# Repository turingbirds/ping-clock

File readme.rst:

The Ping Clock
==============

Are you ever in a video call, when the other party suddenly freezes mid-sentence, leaving you wondering after a few seconds of silence: is it my connection that's having issues, or theirs? In such situations, one glance at the ping clock dial provides an immediate overview of your internet connection status and health, measured in terms of ping time.

Ping time is the time it takes for a network packet to reach a certain destination host and come back again. Lower is better; for video calls, anything below a few tenths of a second is typically fine. The host can be chosen as a public server with high reliability (for example, google.com or 8.8.8.8), or as something with a special significance (like the hostname of your cloud instance).

If your video call freezes, but the ping clock continues to indicate low ping, there is no need to reset your router; just wait for the other side to come back.

.. table::
   :align: center

   +-------------------------------------------------------------------------------------------------------------------------------------------------------------+
   | 🢧  `Click here for a video of the ping clock in action <https://github.com/turingbirds/ping-clock/blob/master/fig/ping_clock_movie.mp4?raw=true>`_        🢠 |
   +-------------------------------------------------------------------------------------------------------------------------------------------------------------+

.. figure:: fig/ping_clock.jpeg
   :scale: 10 %
   :align: left

Setting up the wifi network and host to ping is done by connecting to the ping clock's wifi access point. After configuration, the outermost hand will update once each second with the latest ping value, while the innermost hand tracks the recent maximum pings, making an intermittent connection easy to see.

.. |screenshot1| image:: fig/screenshot1.png
    :scale: 20%

.. |screenshot2| image:: fig/screenshot2.png
    :scale: 20%

.. table::
   :align: center

   +---------------+---------------+
   | |screenshot2| | |screenshot1| |
   +---------------+---------------+

Hardware
--------

The system is controlled by an ESP32, which connects via wifi and updates the e-paper display, and then performs the ping, computes the desired clock hand angles, and sends this angle via SPI to a second ESP32, which functions exclusively as a motor controller.

.. image:: fig/diag.png
   :alt: System block diagram

For mounting the components to the frontplate, a template is provided in `frontplate-cad/frontplate_cnc.pdf <https://github.com/turingbirds/ping-clock/blob/master/frontplate-cad/frontplate_cnc.pdf>`_. Drill out all the holes marked in pink, then drill out all the M3 screw holes at half depth in a larger diameter, to create holes for the countersunk screw heads. The frontplate decal then lies flat against the front, covering all the screws. The front of the e-paper display is pressed against the back of the faceplace, held in place by two aluminium bars covered in a layer of foam.
   
.. image:: fig/ping_clock_rear.jpeg
   :alt: Rear view of the ping clock

The clock is powered from a 5 V DC supply, and consumes approximately 2 W of power. The ESP32s and motor driver ICs are mounted on a custom PCB (see `pcb/ping_clock_mounting_pcb.* <pcb/>`_). 

Dual clock hands motor module
~~~~~~~~~~~~~~~~~~~~~~~~~~~~~

Each hand is actuated by a three-phase brushless DC (BLDC) motor. Actuation is 'direct drive': the hands are mounted directly onto the rotating surface of the motors via two 3D printed hubs.

.. image:: fig/dual_motor_assembly.jpeg
   :alt: The dual motor assembly by itself

BLDC motors can be easily controlled as open-loop servos (akin to stepper motors), with reliable tracking over long timescales provided that the load torque is minimal and that acceleration is bounded. An optical reflection light sensor provides an absolute reference point or 'zero angle'. The motor controller ESP32 generates three-channel PWM drive signals for each motor, following a trapezoidal commutation scheme.

PCBs are 1.2 mm, with black solder mask to reduce ambient light for the optical sensors. All three PCBs (`pcb/motor_module_pcb.* <pcb/>`_) are identical, but only two of them need to have a reflection sensor mounted. The dimensions (width x depth x height) of the assembly, ignoring the protruding hubs, is 50 x 50 x 44 mm. The height is 2 * 18 (spacers) + 3 * 1.2 (PCBs) + 2 * 2.2 (thin M4 nuts) = 44 mm.

Hubs
~~~~

The hubs can be 3D printed using the stereolithographic (resin/UV) method. The outer hub is shown first and contains an outer M5 thread to facilitate mounting the corresponding hand. It has a hollow core, which allows the threaded rod of the inner hand assembly to pass through.

.. image:: fig/hub_outer.png
   :alt: 3D view of the outer hub in OpenSCAD

The inner hub provides an inner M3 thread, that seats a short section of threaded rod, which sticks through the other hub and to the front of the clock faceplate.

.. image:: fig/hub_inner.png
   :alt: 3D view of the inner hub in OpenSCAD

The hands are mounted using the threads provided:

- Central axis: M3 (3 mm diameter) threaded rod

  The hand is pressed between a thin M3 nut and an M3 capped nut.

- Hub axis: M5 (5 mm diameter), threaded
  
  The hand is pressed between two thin M5 nuts. A single M5 rivet could potentially also be used, extending into the clock, to reduce the height that is necessary above the faceplate.

.. image:: fig/hands_mount.jpeg
   :alt: Mounting the clock hands

It is advisable to post-process the 3D printed threads by going over the threads with an M3 and M5 tap, and to drill out the hollow core on the outer hub using a 3.2 mm drill.

Frontplate
~~~~~~~~~~

The frontplate is made out of polycarbonate, in a circular shape, thickness = 4 mm, diameter = 275 (visible portion) + 2*7.5 (behind the metal rim on either side) = 290 mm.

The frontplate graphics can be printed on A3 size paper. A better alternative is to get it as a vinyl sticker.

Note that not all of the display pixels are visible with the current cutout dimensions. This is by design, but you can make the cutout larger to reveal a larger area of the display.

Rim
~~~

Reused from Ikea clock, diameter = 275 mm (dial), 300 mm (overall).

Bill of materials
-----------------

Hardware
~~~~~~~~

(shipping costs excluded)

.. csv-table:: Bill of materials
   :header: "€", "Description"

   "57.19", "7.5"", 800x480 pixel e-paper display https://www.waveshare.com/w/upload/6/60/7.5inch_e-Paper_V2_Specification.pdf"
   "14.92", "Frontplate https://kunststofplatenshop.nl/product/polycarbonaat-helder-4-mm/"
   "6.20", "TB6612FNG motor driver IC (qty: 3)"
   "4", "SFH9201 optical sensor (qty: 2)"
   "7.71", "motor assembly PCBs, color: black, thickness: 1.2mm (seeedstudio; qty: 3)"
   "1.66", "3D printing of the hubs (dirtypcbs.com)"
   "5", "System PCB, color: any, thickness: 1.6 mm (seeedstudio)"
   "14", "frontplate laser-cut vinyl sticker (note: printing this on A3 size paper and cutting it out by hand is a cheaper alternative)"
   "0.10", "motor position sticker (qty: 2)"
   "1", "screws 2mm flat head (qty: 8)"
   "1", "screws 2.5mm flat head (qty: 8)"
   "1", "screws 3mm countersunk head (qty: 16)"
   "1", "M3 nut (qty: 36)"
   "1", "thin M4 nut (qty: 8)"
   "0.50", "M3 threaded rod"
   "1", "M4 threaded rod"
   "0.10", "thin M5 nut (qty: 2)"
   "0.10", "thin M3 nut"
   "0.10", "M3 capped nut"
   "0.55", "vinyl spacer, h = 18 mm, inner d = 4 mm, outer d = 7 mm (qty: 8)"
   "13.69", "BLDC motor with hollow axis (qty: 2)"
   "7.14", "ESP32-DEVKIT (qty: 2)"
   "1", "USB-A PCB mount connector"
   "1", "500 mA fuse and holder"
   "1", "0.1"" IDC headers"
   "1", "0.1"" IDC cables"
   "0.10", "470 R resistor 1206 (qty: 3)"
   "0.10", "47k R resistor 1206 (qty: 2)"
   "0.10", "100 nF capacitor 1206 (qty: 10)"
   "0.10", "10 uF tantal capacitor SMD"
   "5", "Ikea clock (second hand, for the rim and glass)"
   "", ""
   "148.36", "**Total**"

Software
~~~~~~~~

Comfortaa font <aajohan@gmail.com> SIL Open Font License, Version 1.1

Luxi font copyright (c) 2001 by Bigelow & Holmes Inc.

Ping code from https://github.com/marian-craciunescu/ESP32Ping (LGPL-2.1 license).

log2fix code from https://github.com/dmoulding/log2fix (MIT license).

Credits
-------

With gratitude to `Jan Breemer <http://www.breem.nl/>`_ for debugging the 3D model of the hubs and help with the prototype!

License
-------

`Open source hardware <https://www.oshwa.org/>`_ is hardware for which the design is made publicly available, so that anyone can study, modify, distribute, make, and sell the design or hardware based on that design, subject to the following license conditions.

Hardware licensed under the *CERN Open Hardware Licence Version 2 - Weakly Reciprocal,* a copy of which is included in this repository at `cern_ohl_w_v2.txt <https://github.com/turingbirds/ping-clock/blob/master/cern_ohl_w_v2.txt>`_.

Software licensed under the *Apache License 2.0,* a copy of which is included at `apache_license_2.0.txt <https://github.com/turingbirds/ping-clock/blob/master/apache_license_2.0.txt>`_.

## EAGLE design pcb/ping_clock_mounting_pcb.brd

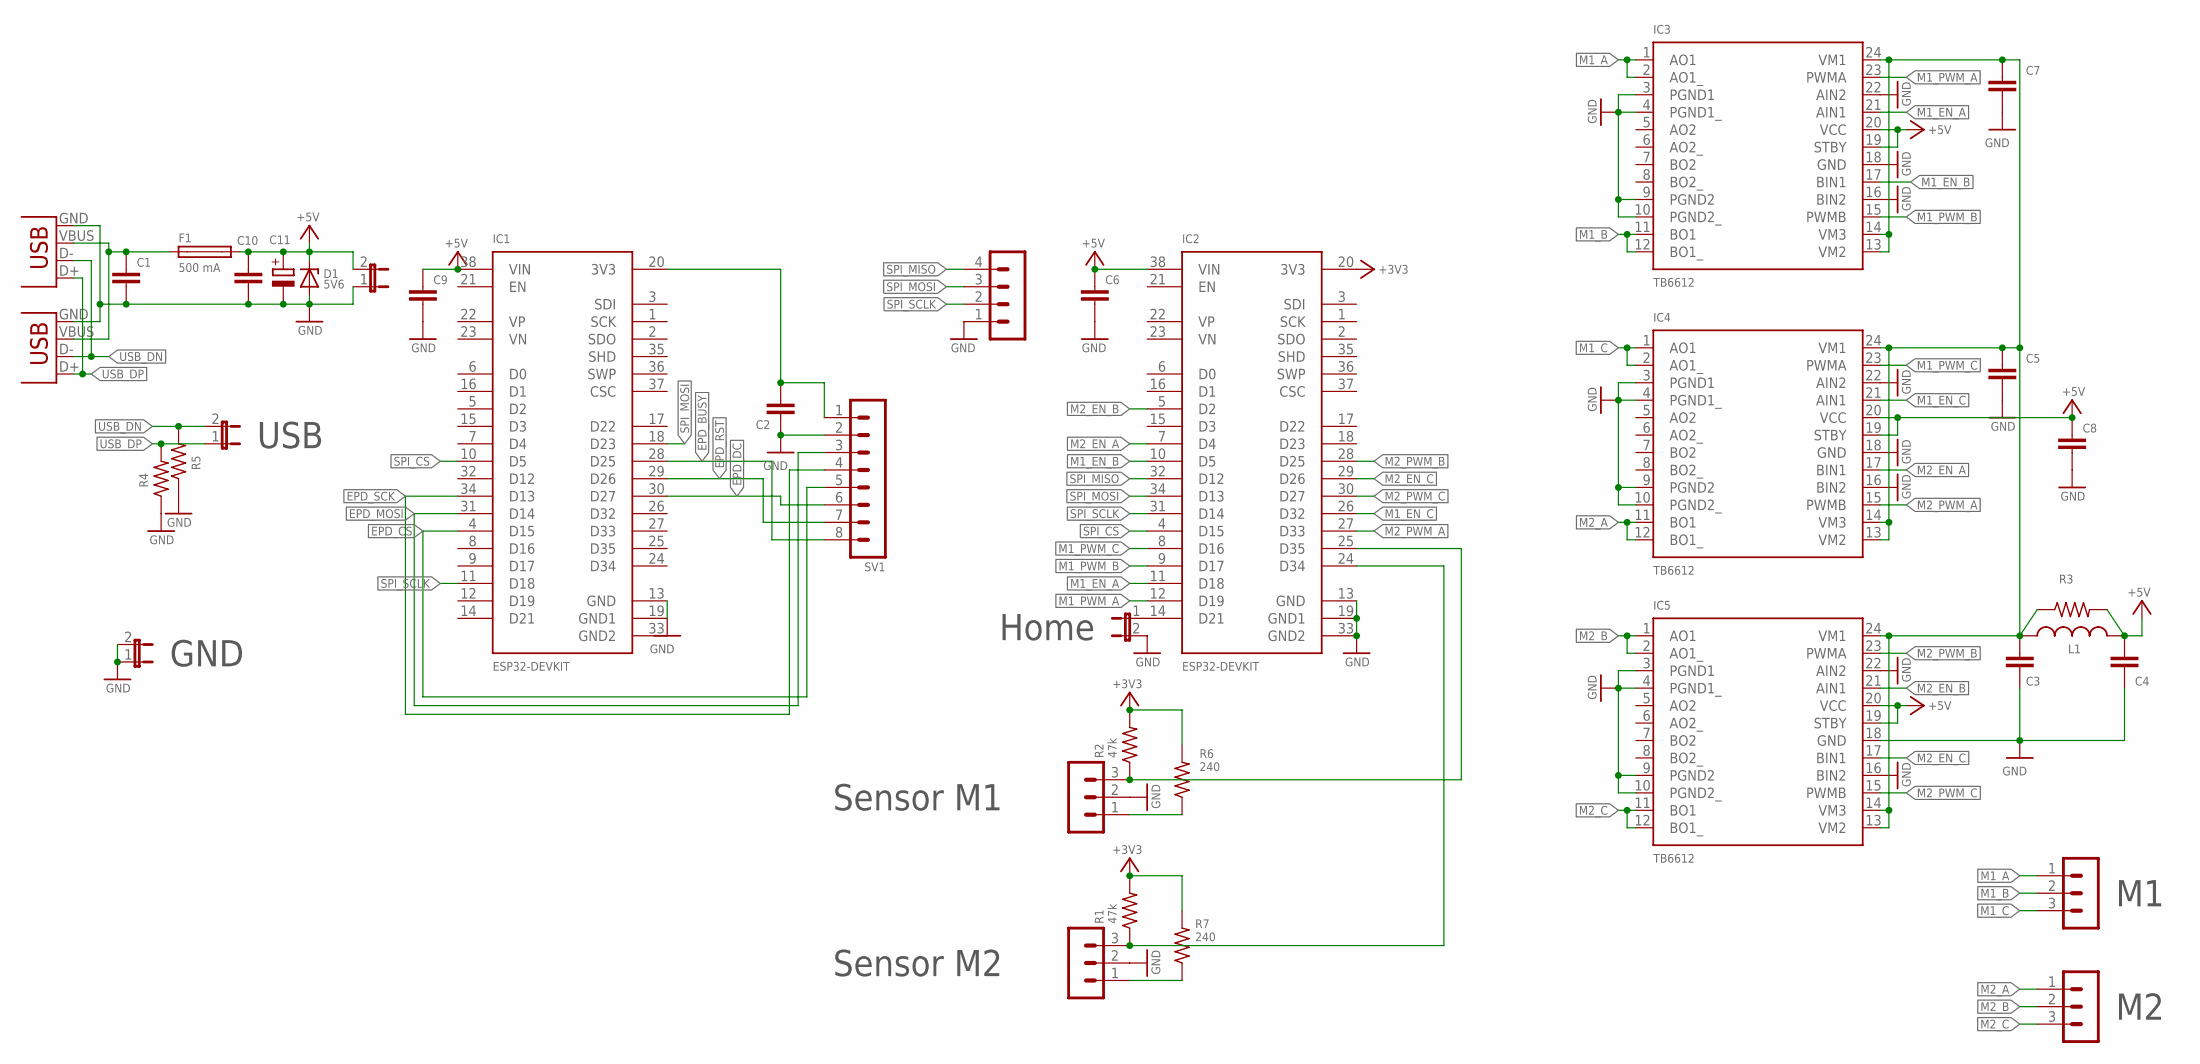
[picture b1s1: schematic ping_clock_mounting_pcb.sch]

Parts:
C1, C2, C3, C4, C5, C6, C7, C8, C9, C10: C-EUC1206; C1206
C11: CPOL-EUD/7343-31R; D/7343-31R
D1: 5V6; DO41Z10
F1: 500 mA; SHK20L
IC1, IC2: ESP32-DEVKIT; MODULE_ESP32_DEVKIT_V1
IC3, IC4, IC5: TB6612; SSOP24
JP1, JP3, JP4, JP5: JP1E; JP1
L1: L-USL3225P; L3225P
R1, R2: 47k; R1206
R3, R4, R5: R-US_R1206; R1206
R6, R7: 240; R1206
SV1: MA08-1
SV2, SV3, SV4, SV5: MA03-1
SV6: MA04-1
X1: USBSMD; USB-MINIB
X2: USBPTH; USB-B-PTH

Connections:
+3V3: IC2.20 (3V3), R1.2, R2.2, R6.2, R7.2
+5V: C4.1, C6.1, C8.1, C9.1, C10.1, C11.+, D1.C, F1.2A (2), IC1.38 (VIN), IC2.38 (VIN), IC3.19 (STBY), IC3.20 (VCC), IC4.19 (STBY), IC4.20 (VCC), IC5.19 (STBY), IC5.20 (VCC), JP5.2, L1.2, R3.2
EPD_BUSY: IC1.28 (D25), SV1.8
EPD_CS: IC1.4 (D15), SV1.5
EPD_DC: IC1.30 (D27), SV1.6
EPD_MOSI: IC1.31 (D14), SV1.3
EPD_RST: IC1.29 (D26), SV1.7
EPD_SCK: IC1.34 (D13), SV1.4
GND: C1.2, C2.1, C3.2, C4.2, C5.2, C6.2, C7.2, C8.2, C9.2, C10.2, C11.-, D1.A, IC1.13 (GND), IC2.13 (GND), IC2.19 (GND1), IC2.33 (GND2), IC3.3 (PGND1), IC3.4 (PGND1_), IC3.9 (PGND2), IC3.10 (PGND2_), IC3.16 (BIN2), IC3.18 (GND), IC3.22 (AIN2), IC4.3 (PGND1), IC4.4 (PGND1_), IC4.9 (PGND2), IC4.10 (PGND2_), IC4.16 (BIN2), IC4.18 (GND), IC4.22 (AIN2), IC5.3 (PGND1), IC5.4 (PGND1_), IC5.9 (PGND2), IC5.10 (PGND2_), IC5.16 (BIN2), IC5.18 (GND), IC5.22 (AIN2), JP1.1, JP1.2, JP4.2, JP5.1, R4.1, R5.1, SV1.2, SV4.2, SV5.2, SV6.1, X1.GND, X2.GND
GND1: IC1.19 (GND1)
GND2: IC1.33 (GND2)
M1_A: IC3.1 (AO1), IC3.2 (AO1_), SV2.1
M1_B: IC3.11 (BO1), IC3.12 (BO1_), SV2.2
M1_C: IC4.1 (AO1), IC4.2 (AO1_), SV2.3
M1_EN_A: IC2.11 (D18), IC3.21 (AIN1)
M1_EN_B: IC2.10 (D5), IC3.17 (BIN1)
M1_EN_C: IC2.26 (D32), IC4.21 (AIN1)
M1_PWM_A: IC2.12 (D19), IC3.23 (PWMA)
M1_PWM_B: IC2.9 (D17), IC3.15 (PWMB)
M1_PWM_C: IC2.8 (D16), IC4.23 (PWMA)
M2_A: IC4.11 (BO1), IC4.12 (BO1_), SV3.1
M2_B: IC5.1 (AO1), IC5.2 (AO1_), SV3.2
M2_C: IC5.11 (BO1), IC5.12 (BO1_), SV3.3
M2_EN_A: IC2.7 (D4), IC4.17 (BIN1)
M2_EN_B: IC2.5 (D2), IC5.21 (AIN1)
M2_EN_C: IC2.29 (D26), IC5.17 (BIN1)
M2_PWM_A: IC2.27 (D33), IC4.15 (PWMB)
M2_PWM_B: IC2.28 (D25), IC5.23 (PWMA)
M2_PWM_C: IC2.30 (D27), IC5.15 (PWMB)
unnamed: IC2.14 (D21), JP4.1
unnamed: C2.2, IC1.20 (3V3), SV1.1
unnamed: C1.1, F1.1A (1), X1.VBUS, X2.VBUS
unnamed: R6.1, SV4.1
unnamed: IC2.24 (D34), R1.1, SV5.3
unnamed: R7.1, SV5.1
unnamed: IC2.25 (D35), R2.1, SV4.3
unnamed: C3.1, C5.1, C7.1, IC3.13 (VM2), IC3.14 (VM3), IC3.24 (VM1), IC4.13 (VM2), IC4.14 (VM3), IC4.24 (VM1), IC5.13 (VM2), IC5.14 (VM3), IC5.24 (VM1), L1.1, R3.1
SPI_CS: IC1.10 (D5), IC2.4 (D15)
SPI_MISO: IC2.32 (D12), SV6.4
SPI_MOSI: IC1.18 (D23), IC2.34 (D13), SV6.3
SPI_SCLK: IC1.11 (D18), IC2.31 (D14), SV6.2
USB_DN: JP3.2, R5.2, X1.D-, X2.D-
USB_DP: JP3.1, R4.2, X1.D+, X2.D+

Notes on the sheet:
Home
Sensor M1
Sensor M2
USB
GND

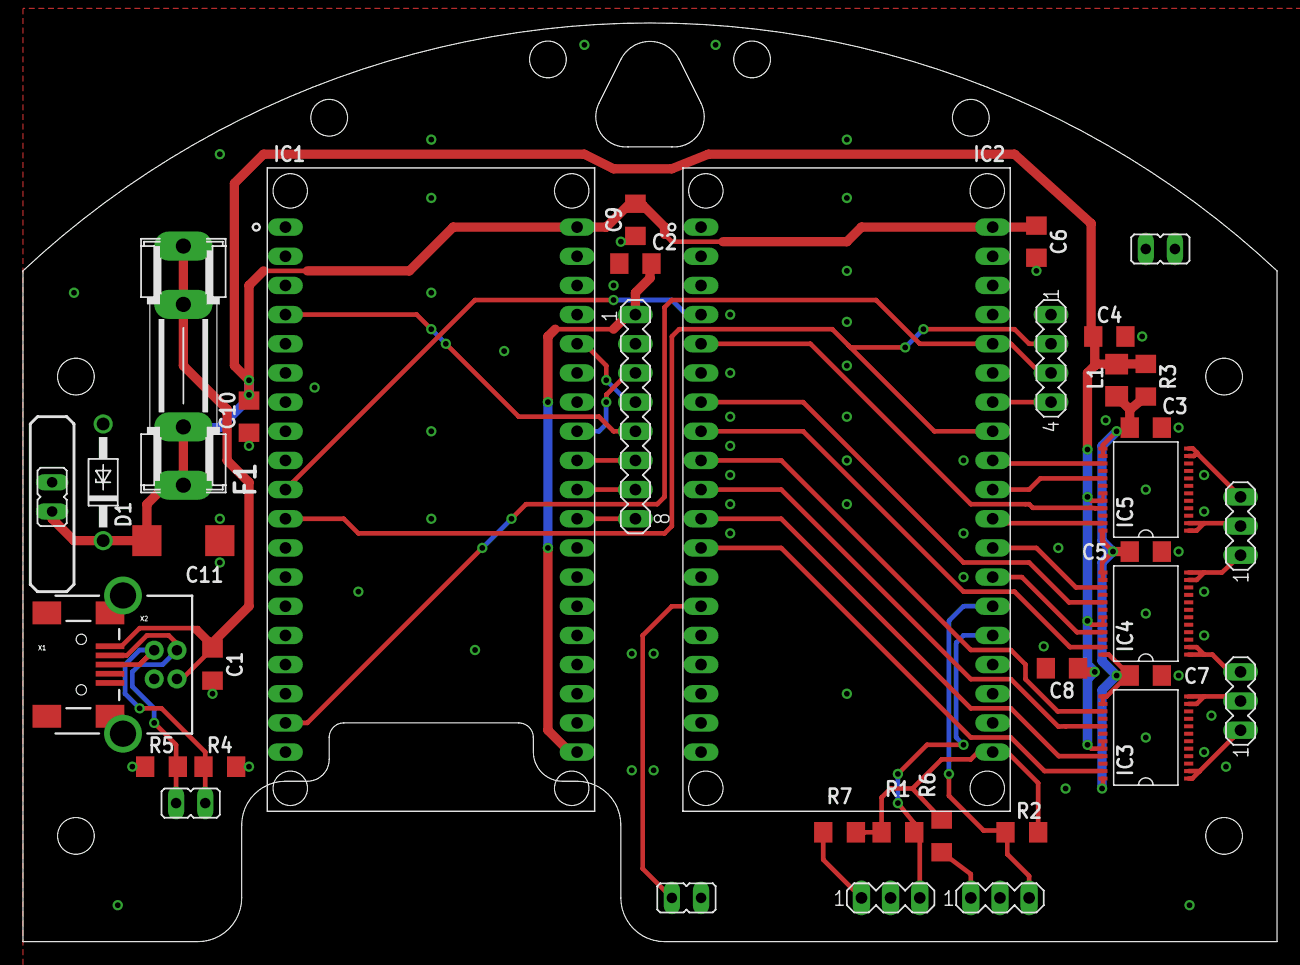
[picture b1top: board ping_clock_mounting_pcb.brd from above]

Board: 2 copper layers, 109.2 x 80.0 mm, 38 parts (0 on the bottom side), 41 nets.

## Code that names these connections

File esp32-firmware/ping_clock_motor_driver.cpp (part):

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
hw_timer_t * timer = NULL;

const int m1_pwm_a_pin = 19;
const int m1_en_a_pin = 18;
const int m1_pwm_b_pin = 17;
const int m1_en_b_pin = 5;
const int m1_pwm_c_pin = 16;
const int m1_en_c_pin = 32;

const int m2_pwm_a_pin = 33;
const int m2_en_a_pin = 4;
const int m2_pwm_b_pin = 25;
const int m2_en_b_pin = 2;
const int m2_pwm_c_pin = 27;
const int m2_en_c_pin = 26;

const int go_to_zero_pin = 21;

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
// setting PWM properties
const int freq = 25000; // pick this above auditory range! [Hz]
const int m1_pwm_a[n_motors] = {0, 3};
const int m1_pwm_b[n_motors] = {1, 4};
const int m1_pwm_c[n_motors] = {2, 5};


/**
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  ledcSetup(m1_pwm_c[1], freq, resolution);

  // attach the channel to the GPIO to be controlled
  ledcAttachPin(m1_pwm_a_pin, m1_pwm_a[0]);
  ledcAttachPin(m1_pwm_b_pin, m1_pwm_b[0]);
  ledcAttachPin(m1_pwm_c_pin, m1_pwm_c[0]);

  ledcAttachPin(m2_pwm_a_pin, m1_pwm_a[1]);
  ledcAttachPin(m2_pwm_b_pin, m1_pwm_b[1]);
  ledcAttachPin(m2_pwm_c_pin, m1_pwm_c[1]);

  digitalWrite(m1_en_a_pin, LOW);
  pinMode(m1_en_a_pin, OUTPUT);
  digitalWrite(m1_en_a_pin, HIGH);

  digitalWrite(m1_en_b_pin, LOW);
  pinMode(m1_en_b_pin, OUTPUT);
  digitalWrite(m1_en_b_pin, HIGH);

  digitalWrite(m1_en_c_pin, LOW);
  pinMode(m1_en_c_pin, OUTPUT);
  digitalWrite(m1_en_c_pin, HIGH);

  digitalWrite(m2_en_a_pin, LOW);
  pinMode(m2_en_a_pin, OUTPUT);
  digitalWrite(m2_en_a_pin, HIGH);

  digitalWrite(m2_en_b_pin, LOW);
  pinMode(m2_en_b_pin, OUTPUT);
  digitalWrite(m2_en_b_pin, HIGH);

  digitalWrite(m2_en_c_pin, LOW);
  pinMode(m2_en_c_pin, OUTPUT);
  digitalWrite(m2_en_c_pin, HIGH);

  pinMode(photo_interruptor_pin[0], INPUT_PULLUP);
  pinMode(photo_interruptor_pin[1], INPUT_PULLUP);
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
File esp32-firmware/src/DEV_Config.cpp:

/*****************************************************************************
* | File      	:   DEV_Config.c
* | Author      :   Waveshare team
* | Function    :   Hardware underlying interface
* | Info        :
*----------------
* |	This version:   V1.0
* | Date        :   2020-02-19
* | Info        :
#
# Permission is hereby granted, free of charge, to any person obtaining a copy
# of this software and associated documnetation files (the "Software"), to deal
# in the Software without restriction, including without limitation the rights
# to use, copy, modify, merge, publish, distribute, sublicense, and/or sell
# copies of the Software, and to permit persons to  whom the Software is
# furished to do so, subject to the following conditions:
#
# The above copyright notice and this permission notice shall be included in
# all copies or substantial portions of the Software.
#
# THE SOFTWARE IS PROVIDED "AS IS", WITHOUT WARRANTY OF ANY KIND, EXPRESS OR
# IMPLIED, INCLUDING BUT NOT LIMITED TO THE WARRANTIES OF MERCHANTABILITY,
# FITNESS OR A PARTICULAR PURPOSE AND NONINFRINGEMENT. IN NO EVENT SHALL THE
# AUTHORS OR COPYRIGHT HOLDERS BE LIABLE FOR ANY CLAIM, DAMAGES OR OTHER
# LIABILITY WHETHER IN AN ACTION OF CONTRACT, TORT OR OTHERWISE, ARISING FROM,
# OUT OF OR IN CONNECTION WITH THE SOFTWARE OR THE USE OR OTHER DEALINGS IN
# THE SOFTWARE.
#
******************************************************************************/
#include "DEV_Config.h"

void GPIO_Config(void)
{
    pinMode(EPD_BUSY_PIN,  INPUT);
    pinMode(EPD_RST_PIN , OUTPUT);
    pinMode(EPD_DC_PIN  , OUTPUT);

    pinMode(EPD_SCK_PIN, OUTPUT);
    pinMode(EPD_MOSI_PIN, OUTPUT);
    pinMode(EPD_CS_PIN , OUTPUT);

    digitalWrite(EPD_CS_PIN , HIGH);
    digitalWrite(EPD_SCK_PIN, LOW);
}
/******************************************************************************
function:	Module Initialize, the BCM2835 library and initialize the pins, SPI protocol
parameter:
Info:
******************************************************************************/
UBYTE DEV_Module_Init(void)
{
	//gpio
	GPIO_Config();

	//serial printf
	//Serial.begin(115200);

	// spi
	// SPI.setDataMode(SPI_MODE0);
	// SPI.setBitOrder(MSBFIRST);
	// SPI.setClockDivider(SPI_CLOCK_DIV4);
	// SPI.begin();

	return 0;
}

/******************************************************************************
function:
			SPI read and write
******************************************************************************/
void DEV_SPI_WriteByte(UBYTE data)
{
    //SPI.beginTransaction(spi_settings);
    digitalWrite(EPD_CS_PIN, GPIO_PIN_RESET);

    for (int i = 0; i < 8; i++)
    {
        if ((data & 0x80) == 0) digitalWrite(EPD_MOSI_PIN, GPIO_PIN_RESET);
        else                    digitalWrite(EPD_MOSI_PIN, GPIO_PIN_SET);

        data <<= 1;
        digitalWrite(EPD_SCK_PIN, GPIO_PIN_SET);
        digitalWrite(EPD_SCK_PIN, GPIO_PIN_RESET);
    }

    //SPI.transfer(data);
    digitalWrite(EPD_CS_PIN, GPIO_PIN_SET);
    //SPI.endTransaction();
}

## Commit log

2022-02-10 update readme typesetting
